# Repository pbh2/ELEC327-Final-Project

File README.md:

# ELEC327-Final-Project
By John Reko, Peter Humphreys, and Sean Hamilton

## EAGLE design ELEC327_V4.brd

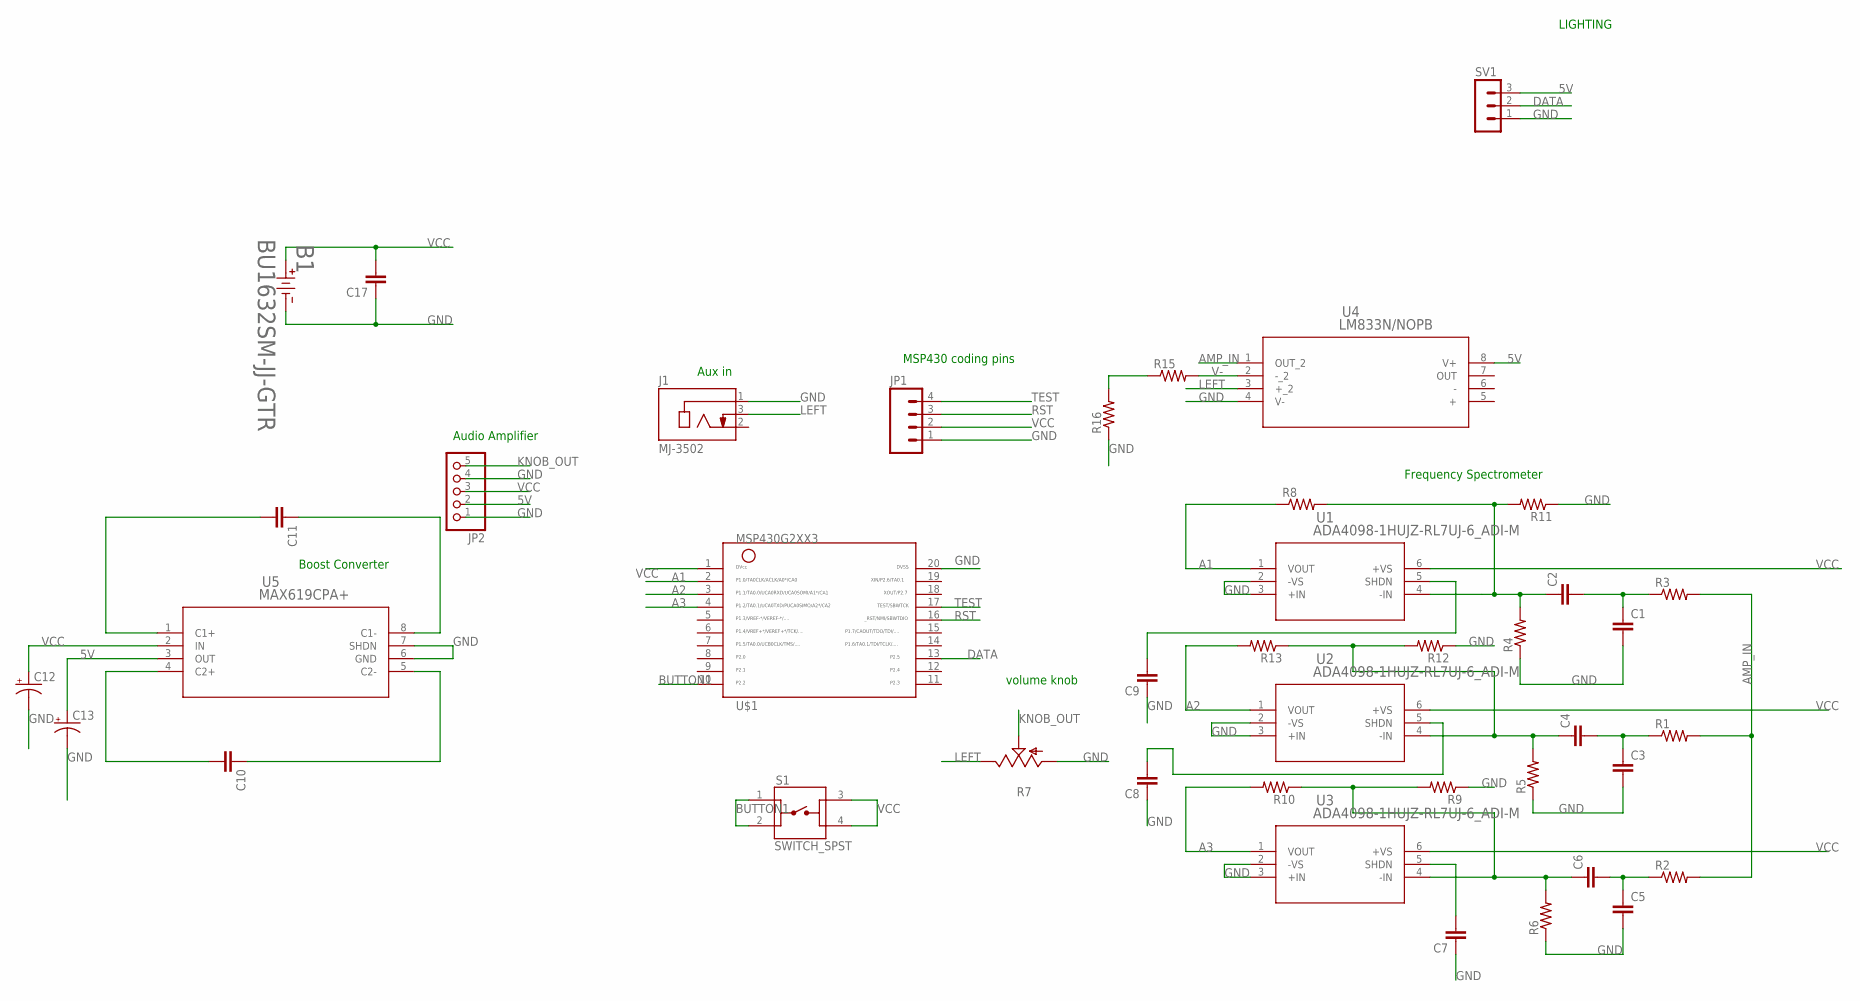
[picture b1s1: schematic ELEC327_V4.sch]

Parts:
B1: BU1632SM-JJ-GTR; BU1632SM-JJ-GTR_MPD
C1, C2, C3, C4, C5, C6, C7, C8, C9, C10, C11, C17: C-EUC1206; C1206
C12, C13: CPOL-USE5-6; E5-6
J1: MJ-3502; CUI_MJ-3502
JP1: HEADER_1X04LOCK; 1X04_LOCK
JP2: PINHD-1X55X2MM; 1_05X2MM
R1, R2, R3, R4, R5, R6, R8, R9, R10, R11, R12, R13, R15, R16: R-US_R1206; R1206
R7: TRIM_US-B25X; B25X
S1: SWITCH_SPST; SW_1825910-7
SV1: MA03-1
U1, U2, U3: ADA4098-1HUJZ-RL7UJ-6_ADI-M; UJ-6_ADI-M
U4: LM833N/NOPB; N08E_TEX
U5: MAX619CPA+; 21-0043D_8_MXM
U$1: MSP430G2XX3TSSOP; PW20

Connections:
5V: C13.+, JP2.2, SV1.3, U4.8 (V+), U5.3 (OUT)
A1: R8.1, U1.1 (VOUT), U$1.2
A2: R13.2, U2.1 (VOUT), U$1.3
A3: R10.2, U3.1 (VOUT), U$1.4
AMP_IN: R1.2, R2.2, R3.2, U4.1 (OUT_2)
BUTTON1: S1.1, S1.2, U$1.10
DATA: SV1.2, U$1.13
GND: B1.2, C1.2, C3.2, C5.2, C7.1, C8.1, C9.1, C12.-, C13.-, C17.1, J1.1, JP1.1, JP2.1, JP2.4, R4.1, R5.1, R6.1, R7.A, R9.1, R11.1, R12.1, R16.1, SV1.1, U1.2 (-VS), U1.3 (+IN), U2.2 (-VS), U2.3 (+IN), U3.2 (-VS), U3.3 (+IN), U4.4 (V-), U5.6 (GND), U5.7 (SHDN), U$1.20
KNOB_OUT: JP2.5, R7.S
LEFT: J1.3, R7.E, U4.3 (+_2)
unnamed: C2.1, R4.2, R8.2, R11.2, U1.4 (-IN)
unnamed: C1.1, C2.2, R3.1
unnamed: C3.1, C4.2, R1.1
unnamed: C5.1, C6.2, R2.1
unnamed: C4.1, R5.2, R12.2, R13.1, U2.4 (-IN)
unnamed: C7.2, U3.5 (SHDN)
unnamed: C6.1, R6.2, R9.2, R10.1, U3.4 (-IN)
unnamed: C8.2, U2.5 (SHDN)
unnamed: C9.2, U1.5 (SHDN)
unnamed: C10.2, U5.4 (C2+)
unnamed: C10.1, U5.5 (C2-)
unnamed: C11.2, U5.1 (C1+)
unnamed: C11.1, U5.8 (C1-)
unnamed: R15.1, R16.2
RST: JP1.3, U$1.16
TEST: JP1.4, U$1.17
V-: R15.2, U4.2 (-_2)
VCC: B1.1, C12.+, C17.2, JP1.2, JP2.3, S1.3, S1.4, U1.6 (+VS), U2.6 (+VS), U3.6 (+VS), U5.2 (IN), U$1.1

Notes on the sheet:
LIGHTING
Audio Amplifier
Boost Converter
Aux in
MSP430 coding pins
volume knob
Frequency Spectrometer

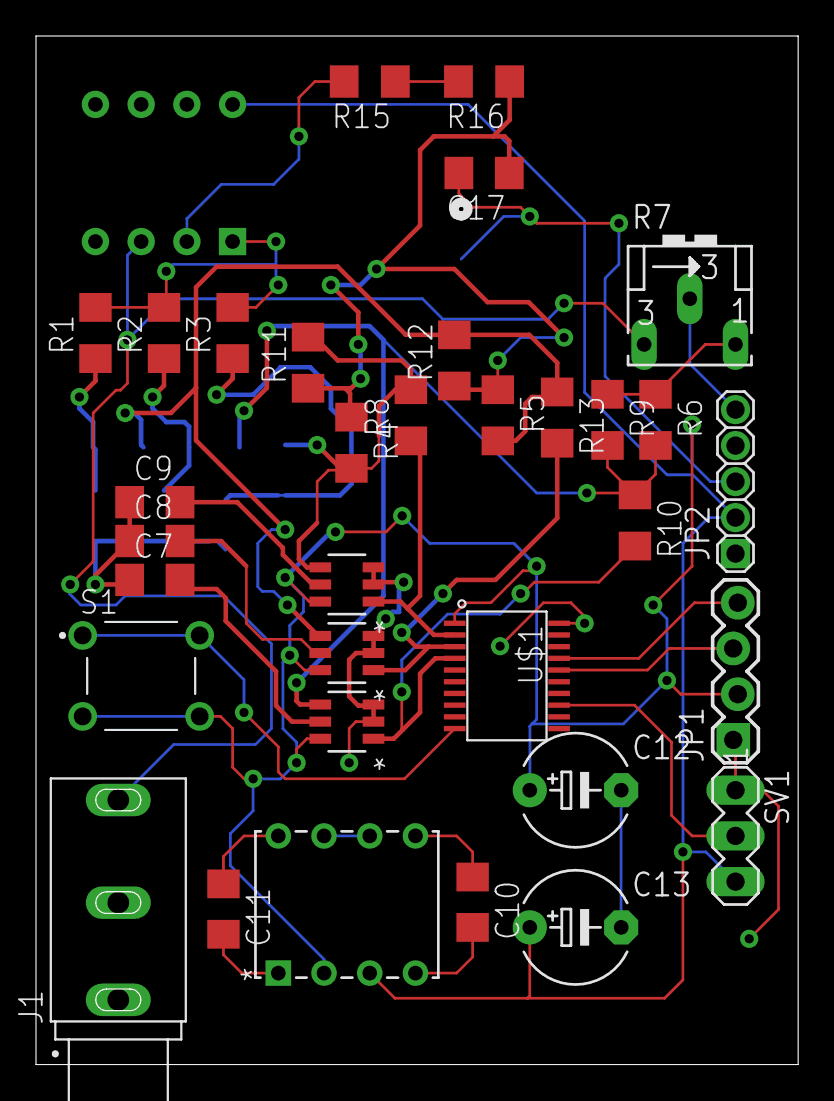
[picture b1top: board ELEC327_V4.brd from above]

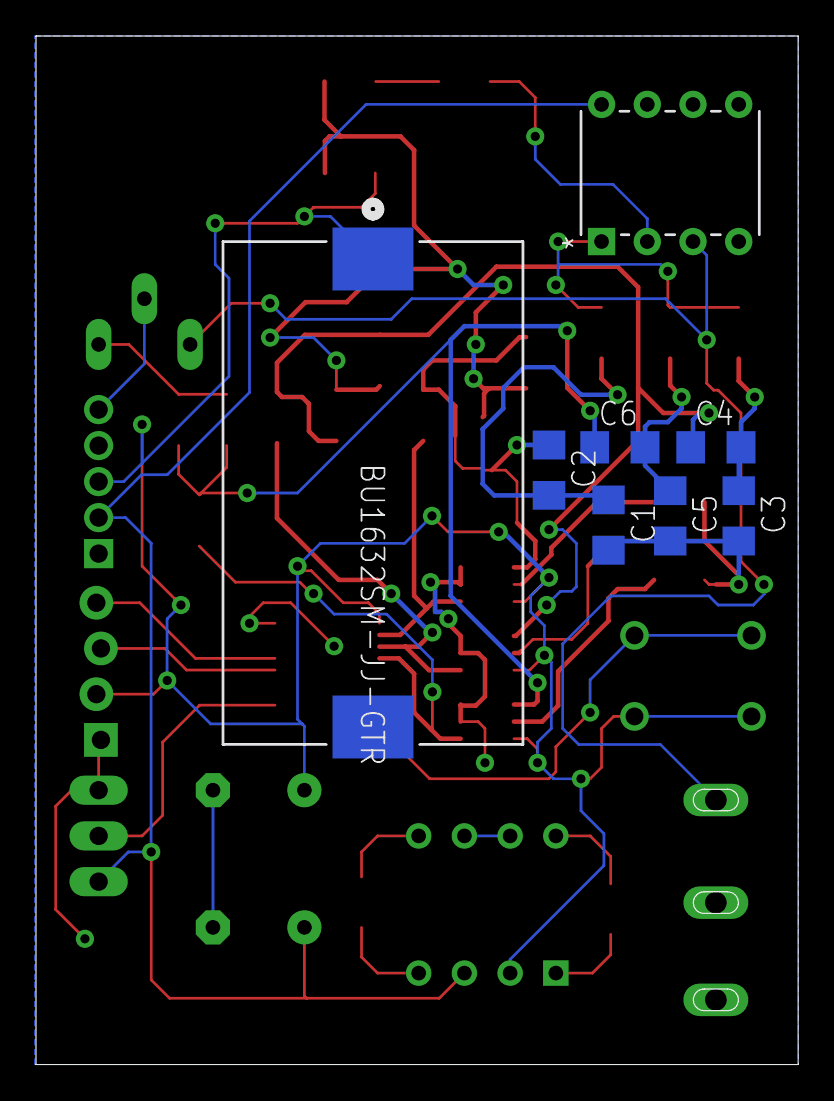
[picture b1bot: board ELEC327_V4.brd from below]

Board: 2 copper layers, 42.3 x 57.1 mm, 41 parts (8 on the bottom side), 28 nets.

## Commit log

2023-05-03 Rename ELEC327_V3.brd to ELEC327_V4.brd

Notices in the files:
parts and their libraries:
COPYRIGHT: Copyright (C) 2023 Ultra Librarian. All rights reserved.
